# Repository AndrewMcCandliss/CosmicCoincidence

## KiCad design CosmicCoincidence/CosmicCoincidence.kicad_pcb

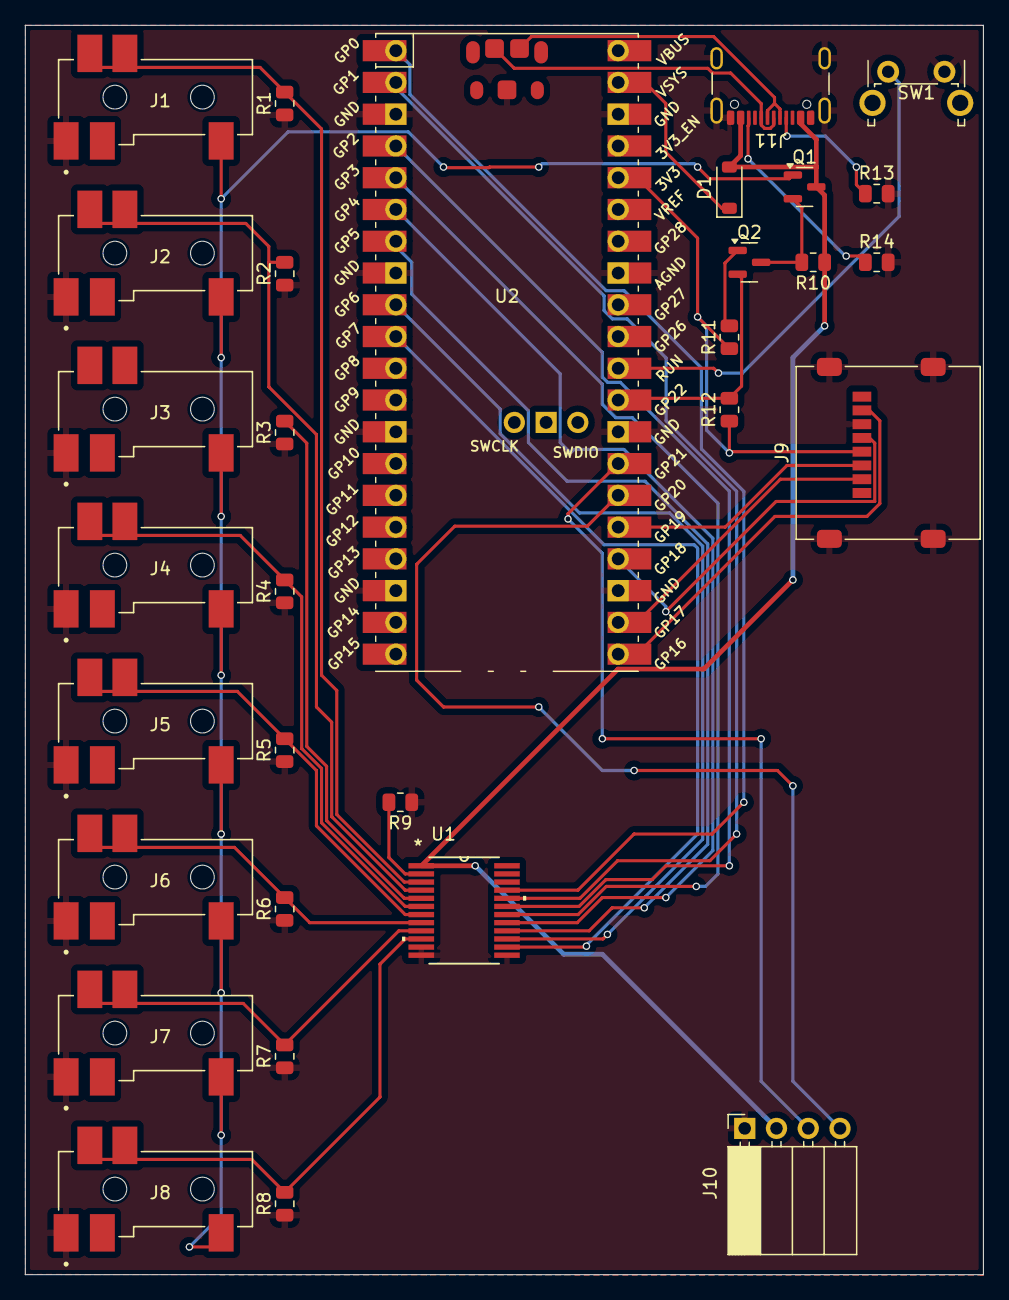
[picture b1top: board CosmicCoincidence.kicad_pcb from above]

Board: 2 copper layers, 76.6 x 99.9 mm, 31 parts (0 on the bottom side), 36 nets.

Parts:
D1: D_Schottky; D_SOD-123
J1, J2, J3, J4, J5, J6, J7, J8: SJ-43515RS-SMT-TR; CUI_SJ-43515RS-SMT-TR
J9: Micro_SD_Card; microSD_HC_Molex_47219-2001
J10: OLED Header; PinSocket_1x04_P2.54mm_Horizontal
J11: USB_C_Receptacle_USB2.0_14P; USB_C_Receptacle_GCT_USB4105-xx-A_16P_TopMnt_Horizontal
Q1: PMOS; SOT-23
Q2: MMBT3904; SOT-23
R1, R2, R3, R4, R5, R6, R7, R8, R9, R10: 10k; R_0805_2012Metric
R11, R12: 22k; R_0805_2012Metric
R13, R14: 5k1; R_0805_2012Metric
SW1: Reset; SW_Tactile_SPST_Angled_PTS645Vx83-2LFS
U1: SN74LVCC3245ADBR; DB24
U2: PicoW; RPi_PicoW_SMD_TH

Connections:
+3V3: J9.4 (VDD), R11.1, R12.1, U1.24 (VCCB), U2.36 (3V3)
+5V: D1.2 (A), J10.2, J11.A4 (VBUS), J11.A9 (VBUS), J11.B4 (VBUS), J11.B9 (VBUS), Q1.3 (S), R10.1, U1.1 (VCCA)
+5V_SWITCHED: J1.2 (T), J2.2 (T), J3.2 (T), J4.2 (T), J5.2 (T), J6.2 (T), J7.2 (T), J8.2 (T), Q1.1 (D)
/ADC0: J11.A5 (CC1), R13.1, U2.31 (GPIO26_ADC0)
/ADC1: J11.B5 (CC2), R14.1, U2.32 (GPIO27_ADC1)
/CS: J9.2 (CS), U2.22 (GPIO17)
/D0: J1.3 (R1), J1.6 (RS), R1.2, U1.3 (A1)
/D1: J2.3 (R1), J2.6 (RS), R2.2, U1.4 (A2)
/D2: J3.3 (R1), J3.6 (RS), R3.2, U1.5 (A3)
/D3: J4.3 (R1), J4.6 (RS), R4.2, U1.6 (A4)
/D4: J5.3 (R1), J5.6 (RS), R5.2, U1.7 (A5)
/D5: J6.3 (R1), J6.6 (RS), R6.2, U1.8 (A6)
/D6: J7.3 (R1), J7.6 (RS), R7.2, U1.9 (A7)
/D7: J8.3 (R1), J8.6 (RS), R8.2, U1.10 (A8)
/GPIO0: U1.21 (B1), U2.1 (GPIO0)
/GPIO1: U1.20 (B2), U2.2 (GPIO1)
/GPIO2: U1.19 (B3), U2.4 (GPIO2)
/GPIO3: U1.18 (B4), U2.5 (GPIO3)
/GPIO4: U1.17 (B5), U2.6 (GPIO4)
/GPIO5: U1.16 (B6), U2.7 (GPIO5)
/GPIO6: U1.15 (B7), U2.9 (GPIO6)
/GPIO7: U1.14 (B8), U2.10 (GPIO7)
/GPIO15: R9.2, U1.2 (DIR)
/GPIO22: Q2.2 (E), R12.2, U2.29 (GPIO22)
/MISO: J9.7 (DO), U2.21 (GPIO16)
/MOSI: J9.3 (DI), U2.25 (GPIO19)
/SCL: J10.3, U2.27 (GPIO21)
/SCLK: J9.5 (SCLK), U2.24 (GPIO18)
/SDA: J10.4, U2.26 (GPIO20)
/USB_DM: J11.A7 (D-), J11.B7 (D-), U2.TP2 (USB_DM)
/USB_DP: J11.A6 (D+), J11.B6 (D+), U2.TP3 (USB_DP)
GND: J1.1 (S), J2.1 (S), J3.1 (S), J4.1 (S), J5.1 (S), J6.1 (S), J7.1 (S), J8.1 (S), J9.6 (VSS), J9.9 (SHIELD), J10.1, J11.A1 (GND), J11.A12 (GND), J11.B1 (GND), J11.B12 (GND), J11.S1 (SHIELD), R1.1, R2.1, R3.1, R4.1, R5.1, R6.1, R7.1, R8.1, R9.1, R13.2, R14.2, SW1.2, U1.11 (GND), U1.12 (GND), U1.13 (GND), U1.22 (*OE), U2.3 (GND), U2.8 (GND), U2.13 (GND), U2.18 (GND), U2.23 (GND), U2.28 (GND), U2.33 (AGND), U2.38 (GND), U2.TP1 (GND)
unnamed: D1.1 (K), U2.39 (VSYS)
unnamed: Q1.2 (G), Q2.3 (C), R10.2
unnamed: Q2.1 (B), R11.2
unnamed: SW1.1, U2.30 (RUN)

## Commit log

2024-07-09 Pulldowns on Data Lines
2024-07-11 Prototype 2
    Changes to trace width and addition of power control, microsd card, and OLED I2C screen
2024-07-11 Prototype 2
    Addition of Power Control, Microsd card, and OLED I2C Screen
2024-07-11 Delete CosmicCoincidence/_autosave-CosmicCoincidence.kicad_sch
    unnecessary file
2024-07-11 Delete CosmicCoincidence/~CosmicCoincidence.kicad_sch.lck
    unnecessary file
2024-07-11 Delete CosmicCoincidence/CosmicCoincidence directory
    accidental addition
2024-07-11 Delete CosmicCoincidence/#auto_saved_files#
    unnecessary file
2024-07-17 Initial Working Code Base
2024-07-17 editor file
2024-07-18 Updated PCB Design (Still no switch footprint)
2024-07-22 clean up schematic; add spice test schematic; change power switching circuit
2024-07-24 Code with send/recieve capability (not working)
2024-07-24 New Arduino Code to enable data sending
